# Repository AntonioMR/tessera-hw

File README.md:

<h1 align="center">Tessera Badge</h1>

<p align="center" width="100%">
  
</p>

***

<p align="center">
  
&nbsp; &nbsp; &nbsp; &nbsp;
  
</p>

***

## SPECIFICATIONS

| Parameter | Value | 
| --- | --- |
| Dimensions | 54.0 × 85.61 mm |

***

## DIRECTORY STRUCTURE

    .
    ├─ Computations       # Misc calculations
    ├─ HTML               # HTML files for generated webpage
    ├─ Images             # Pictures and renders
    │
    ├─ kibot_resources    # External resources for KiBot
    │  ├─ colors          # Color theme for KiCad
    │  ├─ fonts           # Fonts used in the project
    │  ├─ scripts         # External scripts used with KiBot
    │  └─ templates       # Templates for KiBot generated reports
    │
    ├─ kibot_yaml         # KiBot YAML config files
    ├─ KiRI               # KiRI (PCB diff viewer) files
    │
    ├─ lib                # KiCad footprint and symbol libraries
    │  ├─ lib_fp          # Footprint libraries
    │  ├─ lib_packages3d  # Component 3D models
    │  └─ lib_sym         # Symbol libraries
    │
    ├─ Logos              # Logos
    │
    ├─ Manufacturing      # Assembly and fabrication documents
    │  ├─ Assembly        # Assembly documents (BoM, pos, notes)
    │  │
    │  └─ Fabrication     # Fabrication documents (ZIP, notes)
    │     ├─ Drill Tables # CSV drill tables
    │     └─ Gerbers      # Gerbers
    │
    ├─ Report             # Reports for ERC/DRC
    ├─ Schematic          # PDF of schematic
    ├─ Templates          # Title block templates
    ├─ Testing
    │  └─ Testpoints      # Testpoints tables      
    │
    └─ Variants           # Outputs for assembly variants

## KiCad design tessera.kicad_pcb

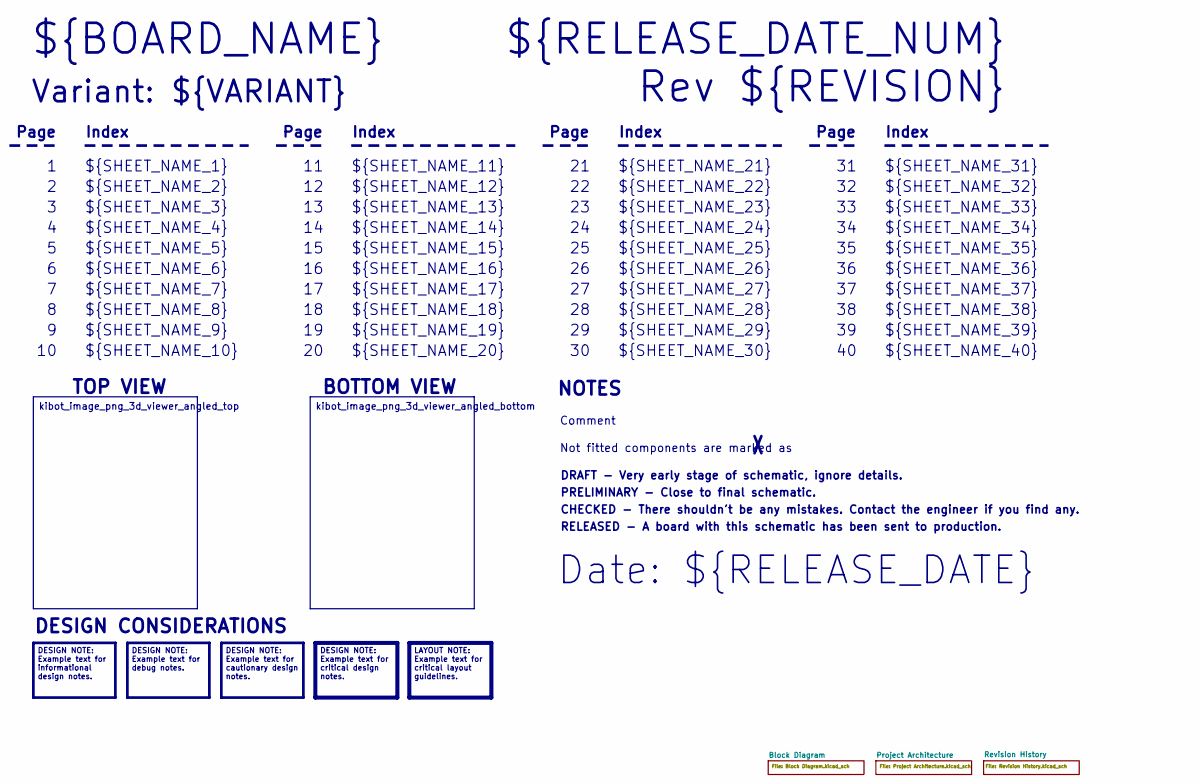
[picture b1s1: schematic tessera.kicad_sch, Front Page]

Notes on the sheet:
DESIGN NOTE: Example text for cautionary design notes.
DESIGN NOTE: Example text for debug notes.
DESIGN NOTE: Example text for critical design notes.
LAYOUT NOTE: Example text for critical layout guidelines.
kibot_image_png_3d_viewer_angled_bottom
DESIGN NOTE: Example text for informational design notes.
kibot_image_png_3d_viewer_angled_top
Variant: ${VARIANT}
RELEASED - A board with this schematic has been sent to production.
${SHEET_NAME_24}
Index
Page
PRELIMINARY - Close to final schematic.
${SHEET_NAME_22}
DRAFT - Very early stage of schematic, ignore details.
${SHEET_NAME_12}
${SHEET_NAME_8}
${SHEET_NAME_2}
${SHEET_NAME_5}
${SHEET_NAME_20}
${SHEET_NAME_23}
${RELEASE_DATE_NUM}
${SHEET_NAME_35}
Not fitted components are marked as
${SHEET_NAME_11}
${SHEET_NAME_6}
${SHEET_NAME_37}
${SHEET_NAME_26}
${SHEET_NAME_36}
Rev ${REVISION}
${SHEET_NAME_15}
CHECKED - There shouldn't be any mistakes. Contact the engineer if you find any.
BOTTOM VIEW
${SHEET_NAME_14}
${SHEET_NAME_21}
${SHEET_NAME_17}
${SHEET_NAME_18}
Date: ${RELEASE_DATE}
${SHEET_NAME_7}
${SHEET_NAME_31}

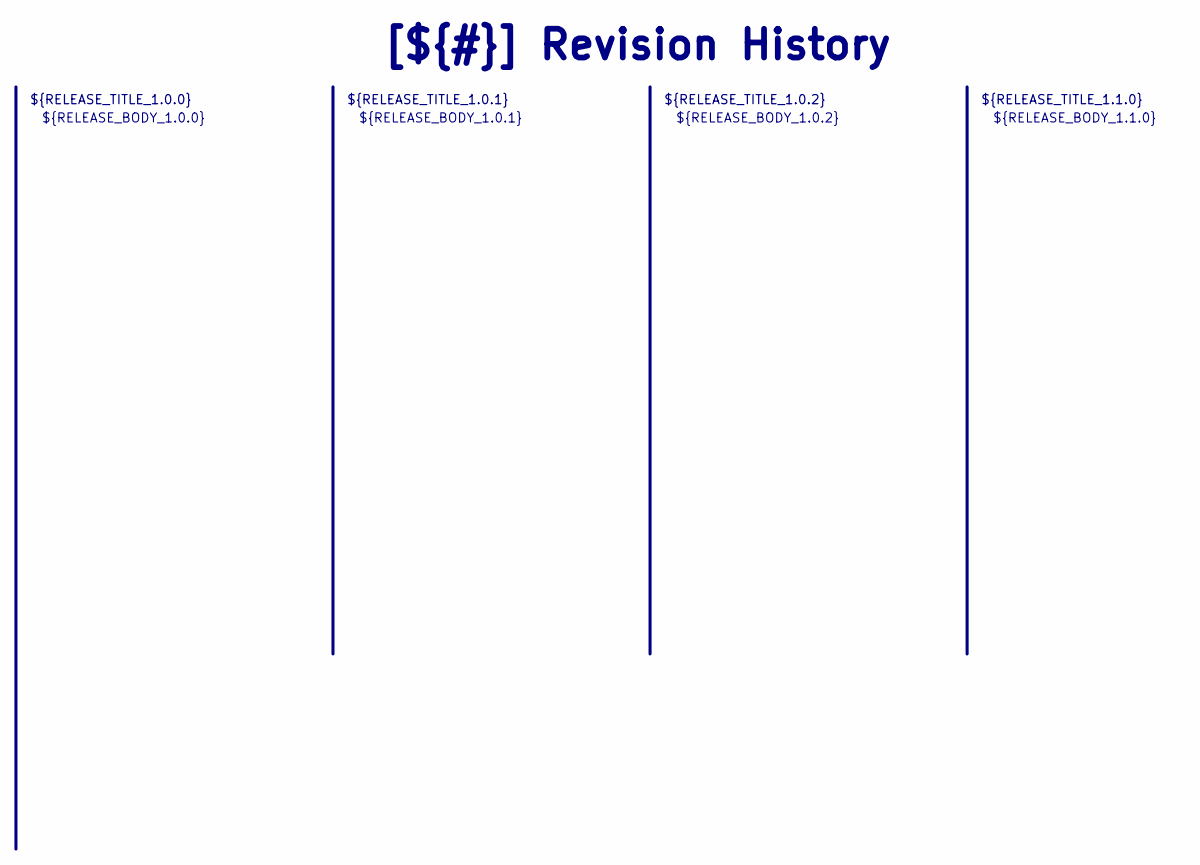
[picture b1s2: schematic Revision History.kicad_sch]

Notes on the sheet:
${RELEASE_BODY_1.1.0}
[${#}] ${TITLE}
${RELEASE_BODY_1.0.0}
${RELEASE_TITLE_1.0.2}
${RELEASE_BODY_1.0.2}
${RELEASE_BODY_1.0.1}
${RELEASE_TITLE_1.0.0}
${RELEASE_TITLE_1.0.1}
${RELEASE_TITLE_1.1.0}

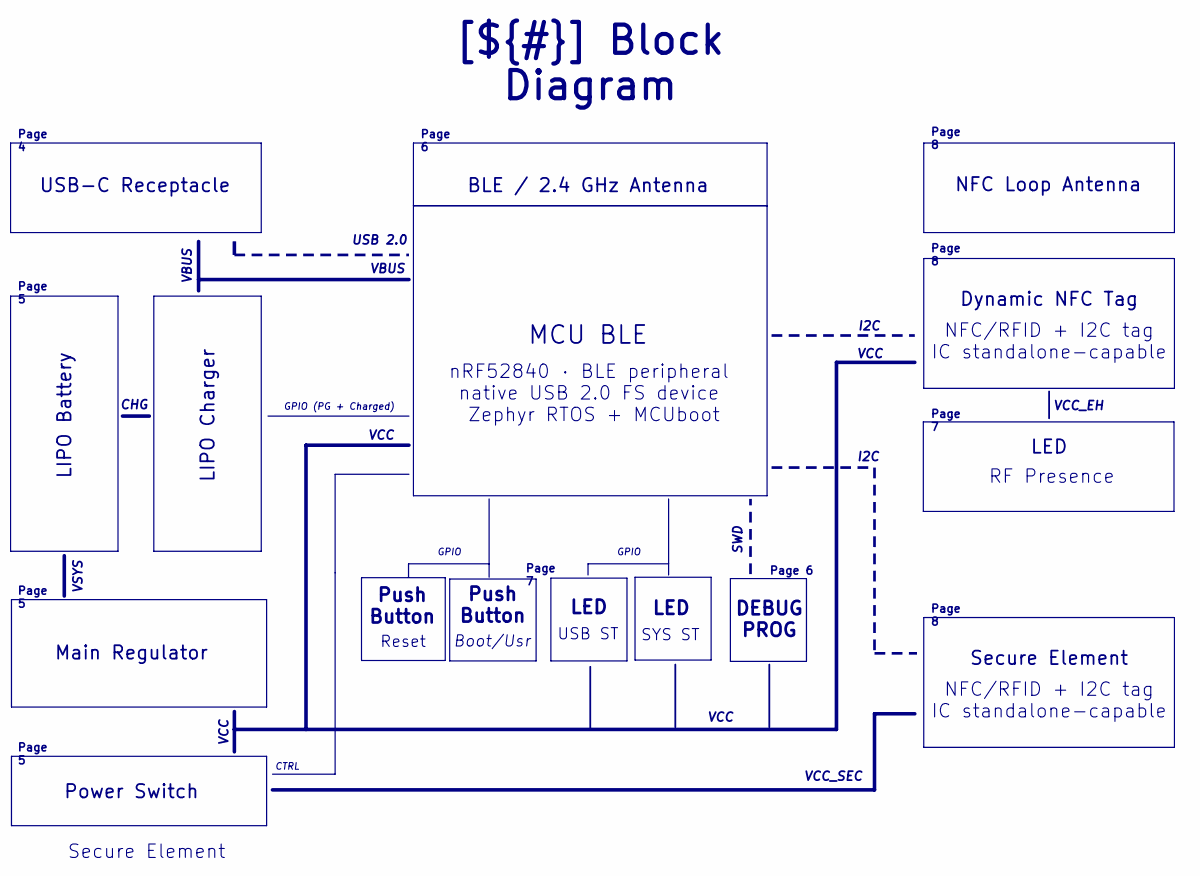
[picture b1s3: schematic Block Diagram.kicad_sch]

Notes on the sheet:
Page 5
Page 6
Page 7
[${#}] ${TITLE}
Page 4
Page 8
Reset
LED
VCC
NFC/RFID + I2C tag IC standalone-capable
USB ST
LIPO Battery
Boot/Usr
I2C
VCC_EH
Dynamic NFC Tag
VBUS
VSYS
CTRL
Secure Element
SYS ST
MCU BLE
BLE / 2.4 GHz Antenna
USB-C Receptacle
Main Regulator
GPIO
GPIO (PG + Charged)
VCC_SEC
Push Button
SWD
LIPO Charger
CHG
NFC Loop Antenna
Secure Element
USB 2.0
nRF52840 · BLE peripheral native USB 2.0 FS device Zephyr RTOS + MCUboot
RF Presence
DEBUG PROG
Power Switch

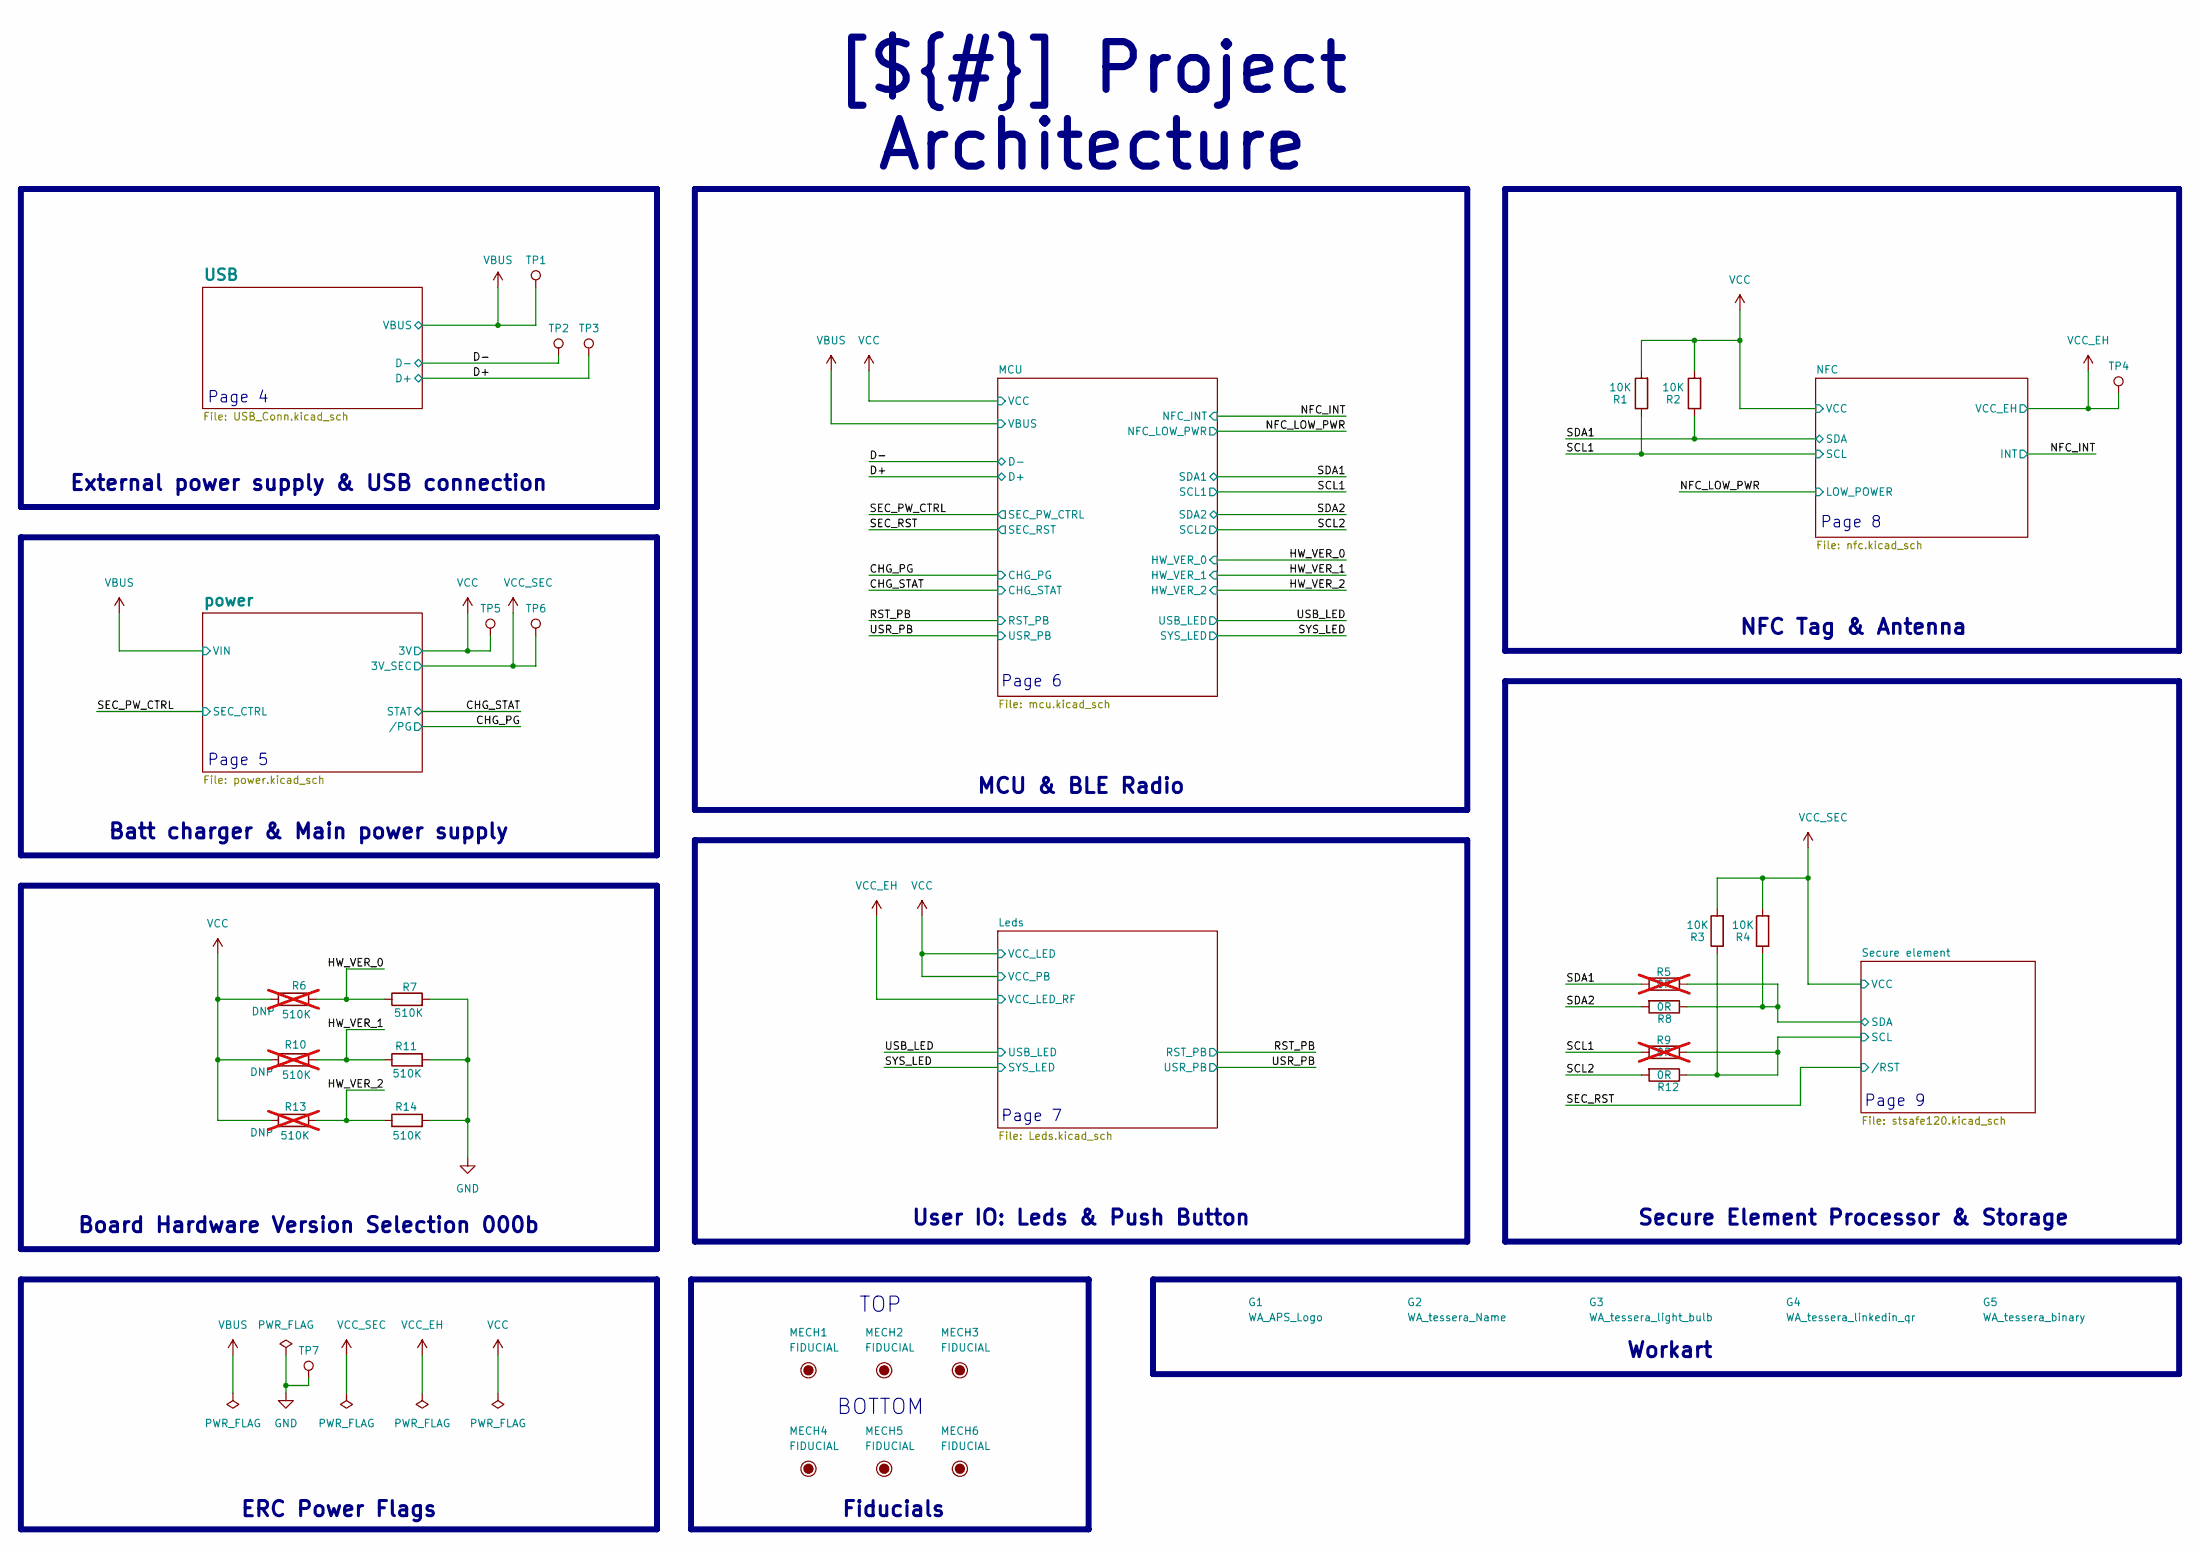
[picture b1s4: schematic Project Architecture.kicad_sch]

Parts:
G1: WA_APS_Logo; logo_aps_4_5
G2: WA_tessera_Name; Name
G3: WA_tessera_light_bulb; light_bulb_8_7_12
G4: WA_tessera_linkedin_qr; linkedin_qr_with_linkedin_logo_inv
G5: WA_tessera_binary; bin_logo
MECH1, MECH2, MECH3, MECH4, MECH5, MECH6: FIDUCIAL; Fiducial_1mm_Mask2mm; Part Number FIDUCIAL_D1_0mm_Mask_2_0mm
R1, R2, R3, R4: 10 kOhms; R_0402_1005Metric; Tolerance ±1%; Part Number R0402_10K_0.063W_±1%
R5, R9: 0R ±5% 1/16W; R_0402_1005Metric; Part Number R0402_0R_0.1W_±5%; not fitted
R6, R10, R13: 510 kOhms; R_0402_1005Metric; Tolerance ±1%; Part Number R0402_510K_0.063W_±1%; not fitted
R7, R11, R14: 510 kOhms; R_0402_1005Metric; Tolerance ±1%; Part Number R0402_510K_0.063W_±1%
R8, R12: 0R ±5% 1/16W; R_0402_1005Metric; Part Number R0402_0R_0.1W_±5%
TP1, TP2, TP3, TP4, TP5, TP6, TP7: TP; TestPoint_Pad_D1.0mm; Part Number TP_SMD_D1_0mm

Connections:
/Project Architecture/D+: TP3.1; also elsewhere on the board
/Project Architecture/D-: TP2.1; also elsewhere on the board
/Project Architecture/HW_VER_0: R6.2, R7.1; also elsewhere on the board
/Project Architecture/HW_VER_1: R10.2, R11.1; also elsewhere on the board
/Project Architecture/HW_VER_2: R13.2, R14.1; also elsewhere on the board
/Project Architecture/SCL1: R1.1, R9.1; also elsewhere on the board
/Project Architecture/SCL2: R12.2; also elsewhere on the board
/Project Architecture/SDA1: R2.1, R5.1; also elsewhere on the board
/Project Architecture/SDA2: R8.2; also elsewhere on the board
/Project Architecture/Secure element/SCL: R3.1, R9.2, R12.1; also elsewhere on the board
/Project Architecture/Secure element/SDA: R4.1, R5.2, R8.1; also elsewhere on the board
GND: R7.2, R11.2, R14.2, TP7.1; also elsewhere on the board
VBUS: TP1.1; also elsewhere on the board
VCC: R1.2, R2.2, R6.1, R10.1, R13.1, TP5.1; also elsewhere on the board
VCC_EH: TP4.1; also elsewhere on the board
VCC_SEC: R3.2, R4.2, TP6.1; also elsewhere on the board

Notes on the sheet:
Board Hardware Version Selection 000b
NFC Tag & Antenna
MCU & BLE Radio
User IO: Leds & Push Button
BOTTOM
TOP
Batt charger & Main power supply
Secure Element Processor & Storage
ERC Power Flags
External power supply & USB connection
Fiducials
Workart
[${#}] ${TITLE}
Page 9
Page 7
Page 6
Page 5
Page 8
Page 4

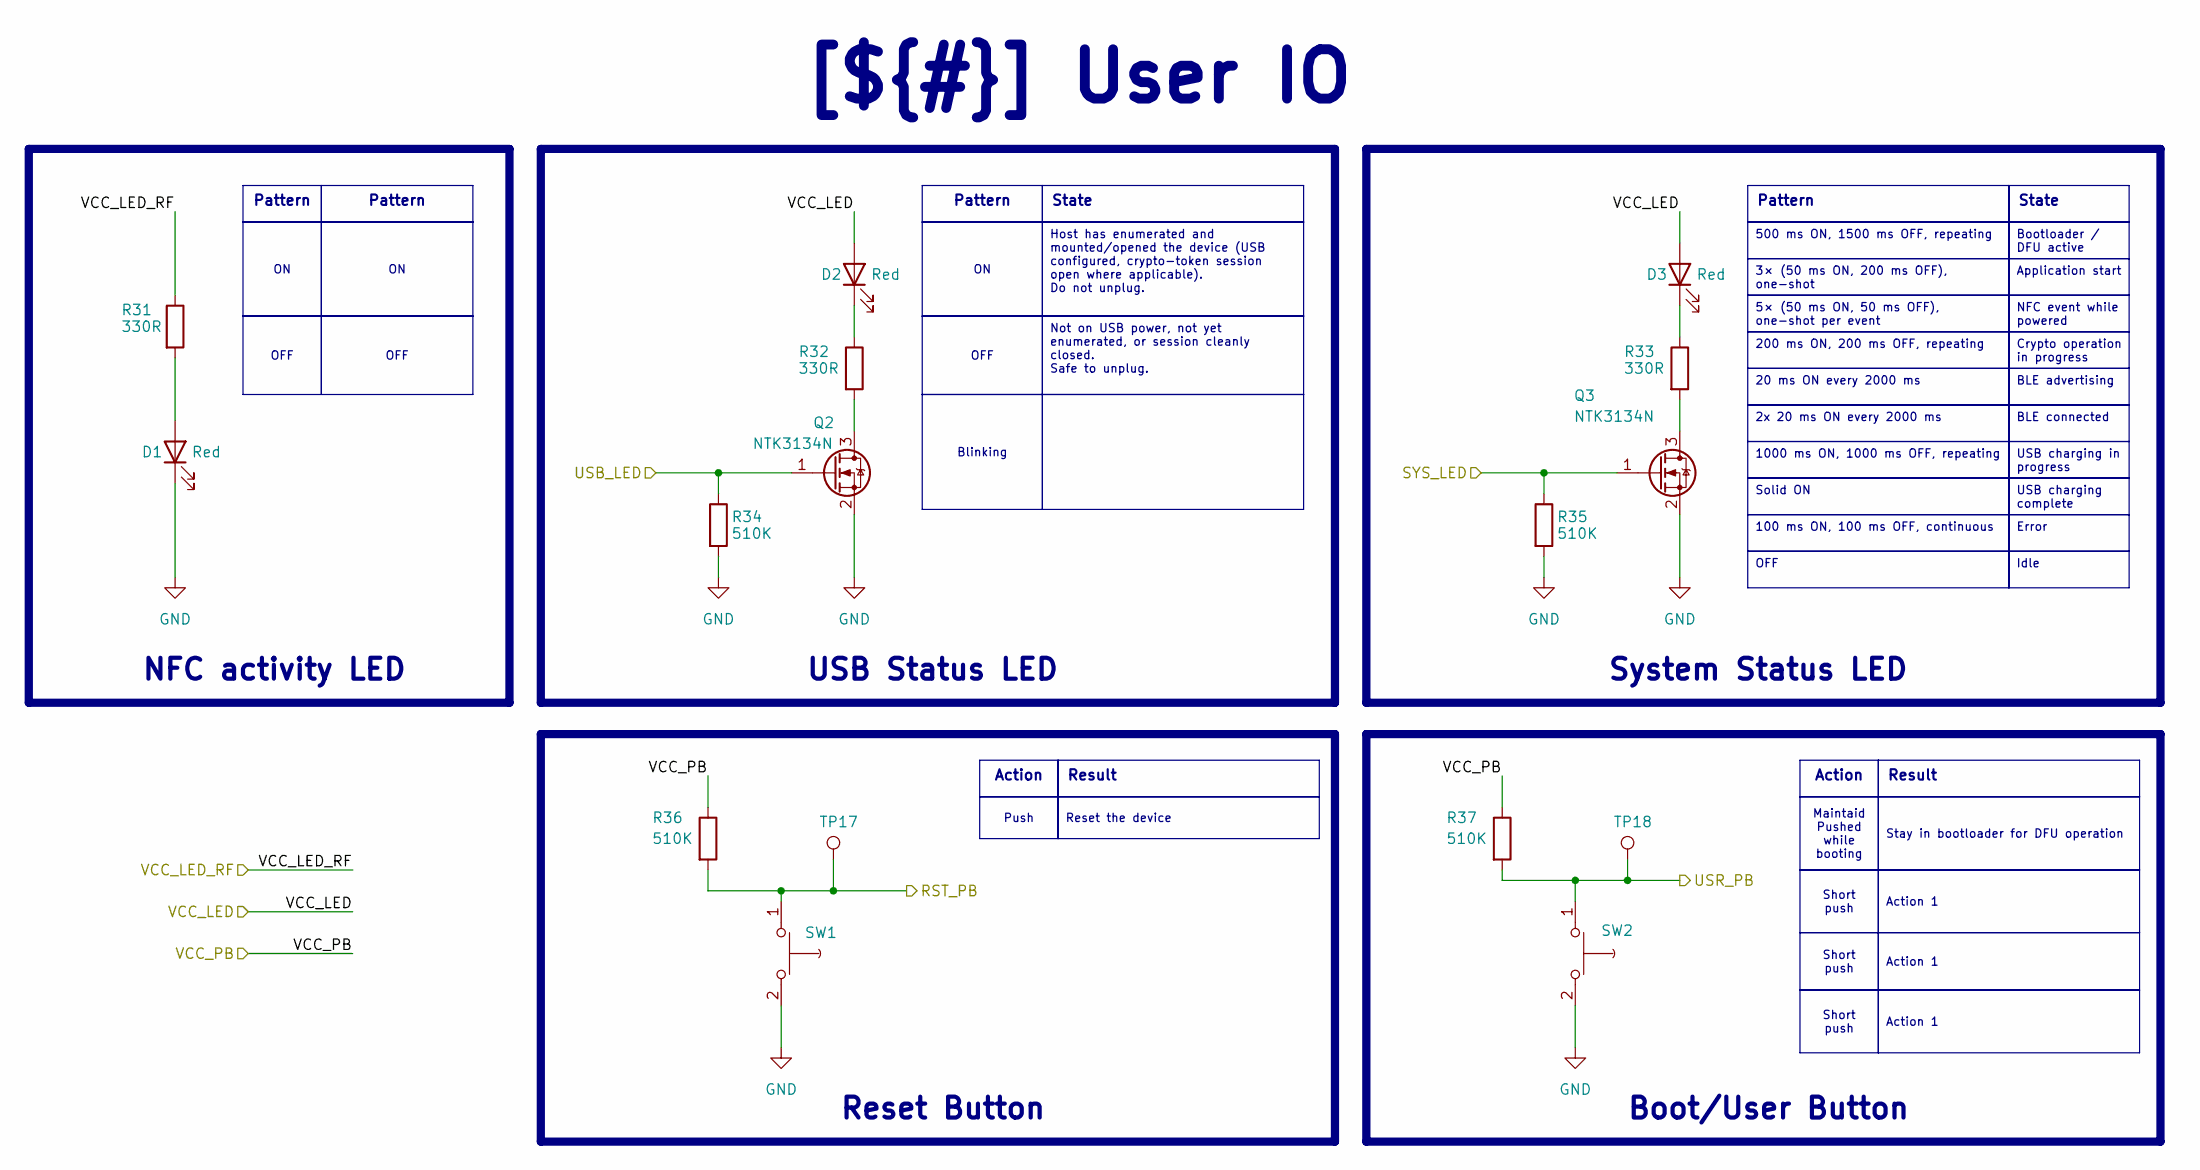
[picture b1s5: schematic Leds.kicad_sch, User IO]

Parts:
D1, D2, D3: APHHS1005SURCK; LED_0402_1005Metric; Part Number APHHS1005SURCK
Q2, Q3: NTK3134N; SOT-723; Part Number NTK3134N
R31, R32, R33: 330R ±1% 1/10W; R_0603_1608Metric; Tolerance ±1%; Part Number R0603_330R_0.1W_±1%
R34, R35, R36, R37: 510 kOhms; R_0402_1005Metric; Tolerance ±1%; Part Number R0402_510K_0.063W_±1%
SW1, SW2: EVQP7A01P; Panasonic_switch_EVQP7K_EVQP7A; Part Number EVQP7A01P
TP17, TP18: TP; TestPoint_Pad_D1.0mm; Part Number TP_SMD_D1_0mm

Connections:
/Project Architecture/RST_PB: R36.2, SW1.1, TP17.1; also elsewhere on the board
/Project Architecture/SYS_LED: Q3.1 (G), R35.1; also elsewhere on the board
/Project Architecture/USB_LED: Q2.1 (G), R34.1; also elsewhere on the board
/Project Architecture/USR_PB: R37.2, SW2.1, TP18.1; also elsewhere on the board
GND: D1.1 (K), Q2.2 (S), Q3.2 (S), R34.2, R35.2, SW1.2, SW2.2; also elsewhere on the board
unnamed: D1.2 (A), R31.2
unnamed: D2.1 (K), R32.1
unnamed: D3.1 (K), R33.1
unnamed: Q2.3 (D), R32.2
unnamed: Q3.3 (D), R33.2
VCC: D2.2 (A), D3.2 (A), R36.1, R37.1; also elsewhere on the board
VCC_EH: R31.1; also elsewhere on the board

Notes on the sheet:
State
OFF
USB charging in progress
Application start
Error
3× (50 ms ON, 200 ms OFF), one-shot
Bootloader / DFU active
Result
Action 1
Short push
Blinking
Solid ON
BLE advertising
Pattern
100 ms ON, 100 ms OFF, continuous
Reset the device
NFC activity LED
USB Status LED
Idle
Action
20 ms ON every 2000 ms
[${#}] ${TITLE}
Boot/User Button
Not on USB power, not yet enumerated, or session cleanly closed. Safe to unplug.
Crypto operation in progress
Host has enumerated and mounted/opened the device (USB configured, crypto-token session open where applicable). Do not unplug.
System Status LED
Maintaid Pushed while booting
Push
Reset Button
2x 20 ms ON every 2000 ms
1000 ms ON, 1000 ms OFF, repeating
USB charging complete
NFC event while powered
BLE connected
500 ms ON, 1500 ms OFF, repeating
Stay in bootloader for DFU operation
200 ms ON, 200 ms OFF, repeating
5× (50 ms ON, 50 ms OFF), one-shot per event

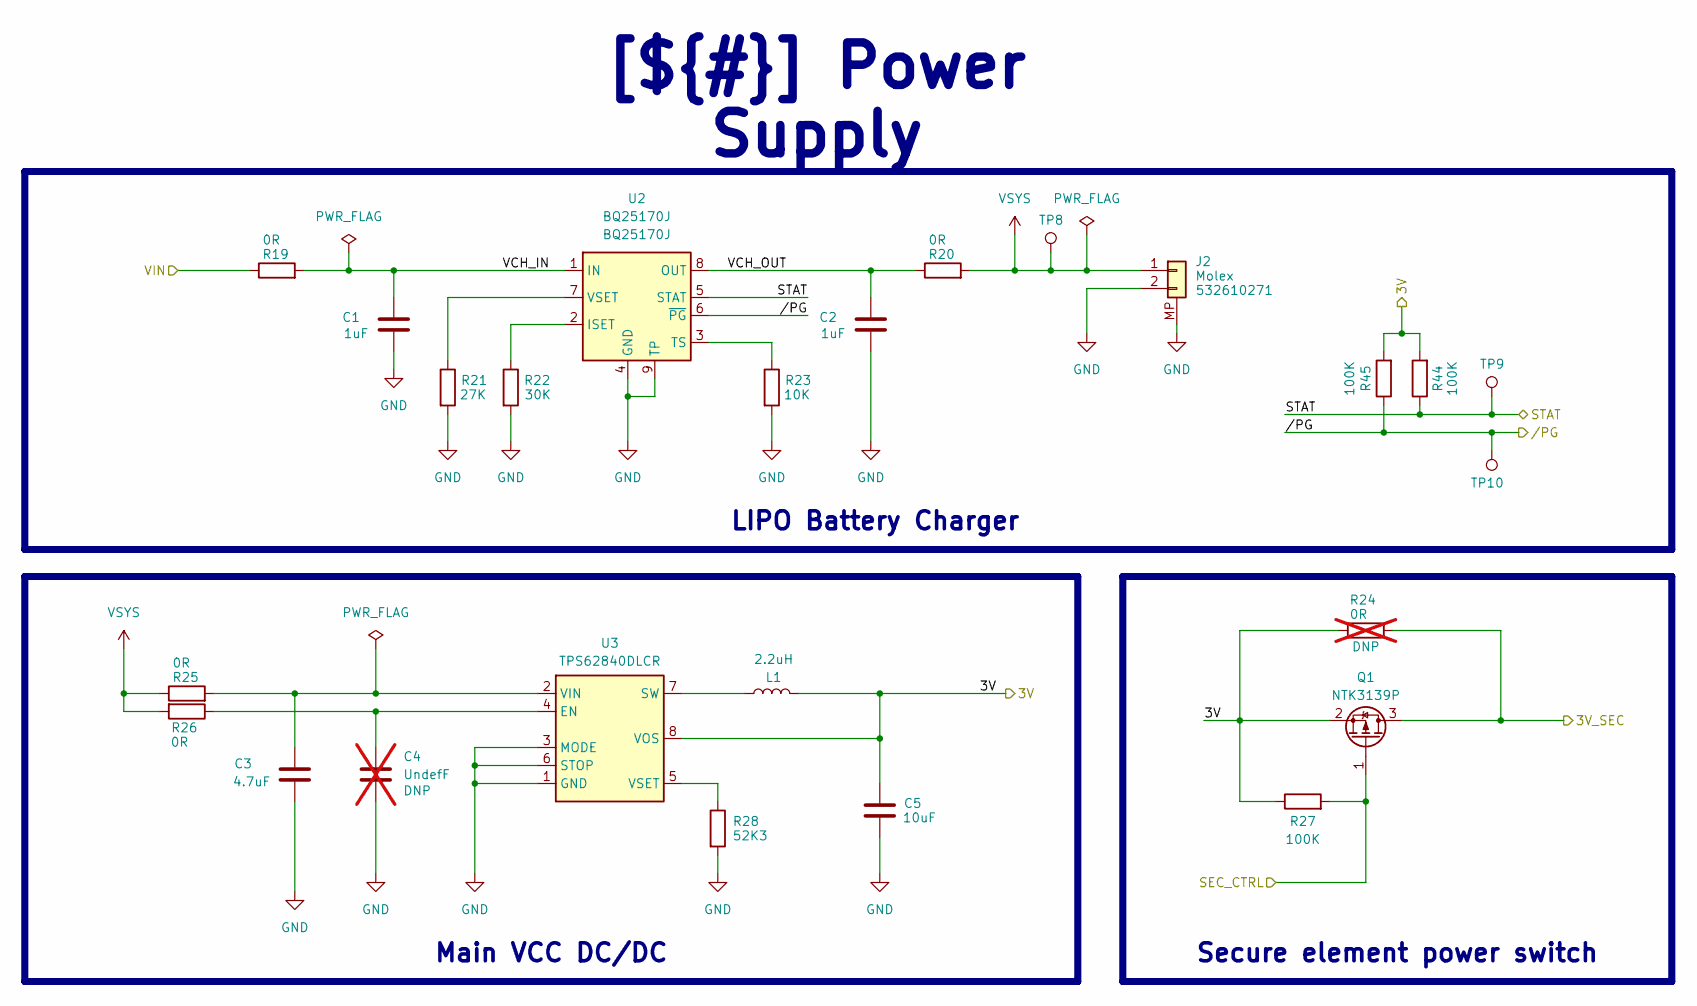
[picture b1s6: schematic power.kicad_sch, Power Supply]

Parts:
C1, C2: 1uF 6.3V (X5R); C_0402_1005Metric; Tolerance ±10%; Voltage 6.3V; Part Number C0402_1uF_6.3V_±10%_X5R
C3: 4.7uF 6.3V (X7R); C_0805_2012Metric; Tolerance ±10%; Voltage 6.3V; Part Number C0805_4.7uF_6.3V_±10%_X7R
C4: UndefF; C_0402_1005Metric; Part Number C0402_Undef; not fitted
C5: 10uF 10V (X7R); C_0805_2012Metric; Tolerance ±10%; Voltage 10V; Part Number C0805_10uF_10V_±10%_X7R
J2: 532610271; Molex_PicoBlade_53261-0271_1x02-1MP_P1.25mm_Horizontal; Voltage 125V; Part Number Molex_PicoBlade_532610271
L1: 2.2uH; L_0806_2016Metric; Tolerance ±20%; Part Number L0806_2.2uH_1.8A_±20%_116mOhm
Q1: NTK3139P; SOT-723; Part Number NTK3139P
R19, R20, R25, R26: 0R ±5% 1/16W; R_0402_1005Metric; Part Number R0402_0R_0.1W_±5%
R21: 27 kOhms; R_0402_1005Metric; Tolerance ±1%; Part Number R0402_27K_0.063W_±1%
R22: 30 kOhms; R_0402_1005Metric; Tolerance ±1%; Part Number R0402_30K_0.063W_±1%
R23: 10 kOhms; R_0402_1005Metric; Tolerance ±1%; Part Number R0402_10K_0.063W_±1%
R24: 0R ±5% 1/16W; R_0402_1005Metric; Part Number R0402_0R_0.1W_±5%; not fitted
R27, R44, R45: 100 kOhms; R_0402_1005Metric; Tolerance ±1%; Part Number R0402_100K_0.063W_±1%
R28: 52.3 kOhms; R_0402_1005Metric; Tolerance ±1%; Part Number R0402_52K3_0.063W_±1%
TP8, TP9, TP10: TP; TestPoint_Pad_D1.0mm; Part Number TP_SMD_D1_0mm
U2: BQ25170J; WSON-8-1EP_2x2mm_P0.5mm_EP0.9x1.6mm; Part Number BQ25170J
U3: TPS62840DLCR; Texas_VSON-HR-8_1.5x2mm_P0.5mm; Part Number TPS62840DLCR

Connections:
/Project Architecture/CHG_PG: R45.1, TP10.1, U2.6 (~PG); also elsewhere on the board
/Project Architecture/CHG_STAT: R44.1, TP9.1, U2.5 (STAT); also elsewhere on the board
/Project Architecture/SEC_PW_CTRL: Q1.1 (G), R27.2; also elsewhere on the board
/Project Architecture/power/VCH_IN: C1.1, R19.2, U2.1 (IN)
/Project Architecture/power/VCH_OUT: C2.1, R20.1, U2.8 (OUT)
GND: C1.2, C2.2, C3.2, C4.2, C5.2, J2.2, J2.MP, R21.2, R22.2, R23.2, R28.2, U2.4 (GND), U2.9 (TP), U3.1 (GND), U3.3 (MODE), U3.6 (STOP); also elsewhere on the board
unnamed: R22.1, U2.2 (ISET)
unnamed: R23.1, U2.3 (TS)
unnamed: R21.1, U2.7 (VSET)
unnamed: C4.1, R26.1, U3.4 (EN)
unnamed: L1.1, U3.7 (SW)
unnamed: C3.1, R25.2, U3.2 (VIN)
unnamed: R28.1, U3.5 (VSET)
VBUS: R19.1; also elsewhere on the board
VCC: C5.1, L1.2, Q1.2 (S), R24.1, R27.1, R44.2, R45.2, U3.8 (VOS); also elsewhere on the board
VCC_SEC: Q1.3 (D), R24.2; also elsewhere on the board
VSYS: J2.1, R20.2, R25.1, R26.2, TP8.1

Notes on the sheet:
LIPO Battery Charger
Secure element power switch
Main VCC DC/DC
[${#}] ${TITLE}

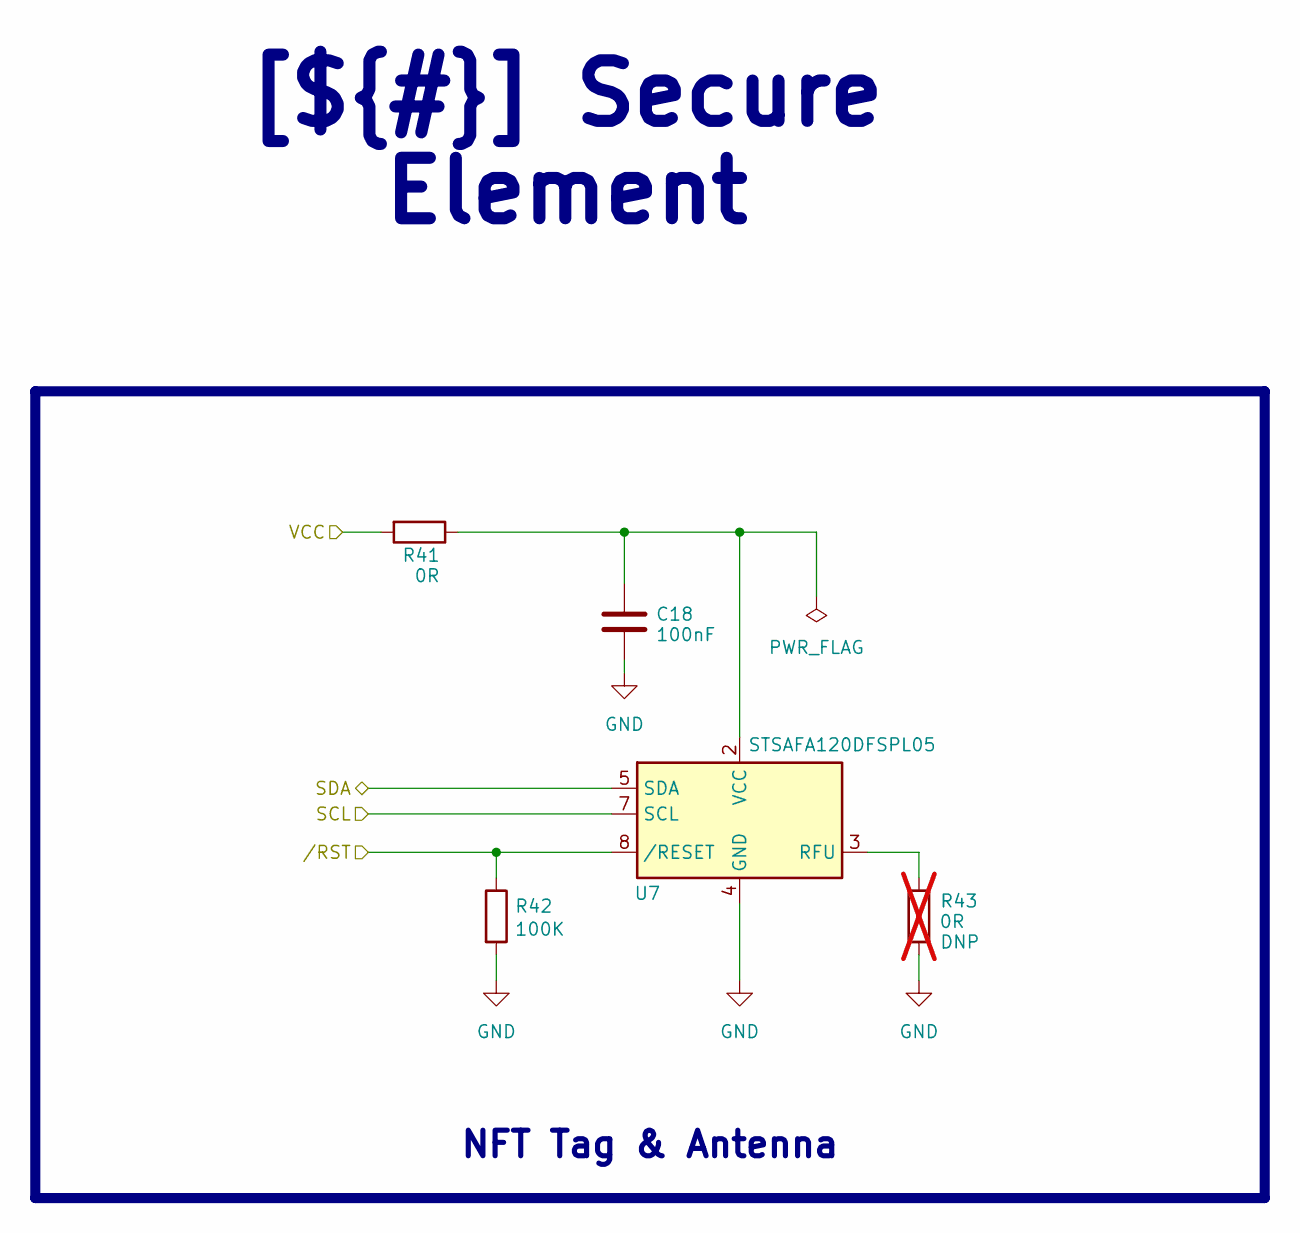
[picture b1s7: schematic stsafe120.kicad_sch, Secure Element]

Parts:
C18: 100nF 16V (X7R); C_0402_1005Metric; Tolerance ±10%; Voltage 16V; Part Number C0402_100nF_16V_±10%_X7R
R41: 0R ±5% 1/16W; R_0402_1005Metric; Part Number R0402_0R_0.1W_±5%
R42: 100 kOhms; R_0402_1005Metric; Tolerance ±1%; Part Number R0402_100K_0.063W_±1%
R43: 0R ±5% 1/16W; R_0402_1005Metric; Part Number R0402_0R_0.1W_±5%; not fitted
U7: STSAFA120DFSPL05; ST_UFDFPN-8-1EP_2x3mm_P0.5mm_EP1.4x2.55mm; Voltage 2.7-5.5 V; Part Number STSAFA120DFSPL05

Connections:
/Project Architecture/SEC_RST: R42.1, U7.8 (/RESET); also elsewhere on the board
/Project Architecture/Secure element/SCL: U7.7 (SCL); also elsewhere on the board
/Project Architecture/Secure element/SDA: U7.5 (SDA); also elsewhere on the board
GND: C18.2, R42.2, R43.2, U7.4 (GND), U7.9 (EP); also elsewhere on the board
unnamed: R43.1, U7.3 (RFU)
unnamed: C18.1, R41.1, U7.2 (VCC)
VCC_SEC: R41.2; also elsewhere on the board

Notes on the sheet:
[${#}] ${TITLE}
NFT Tag & Antenna

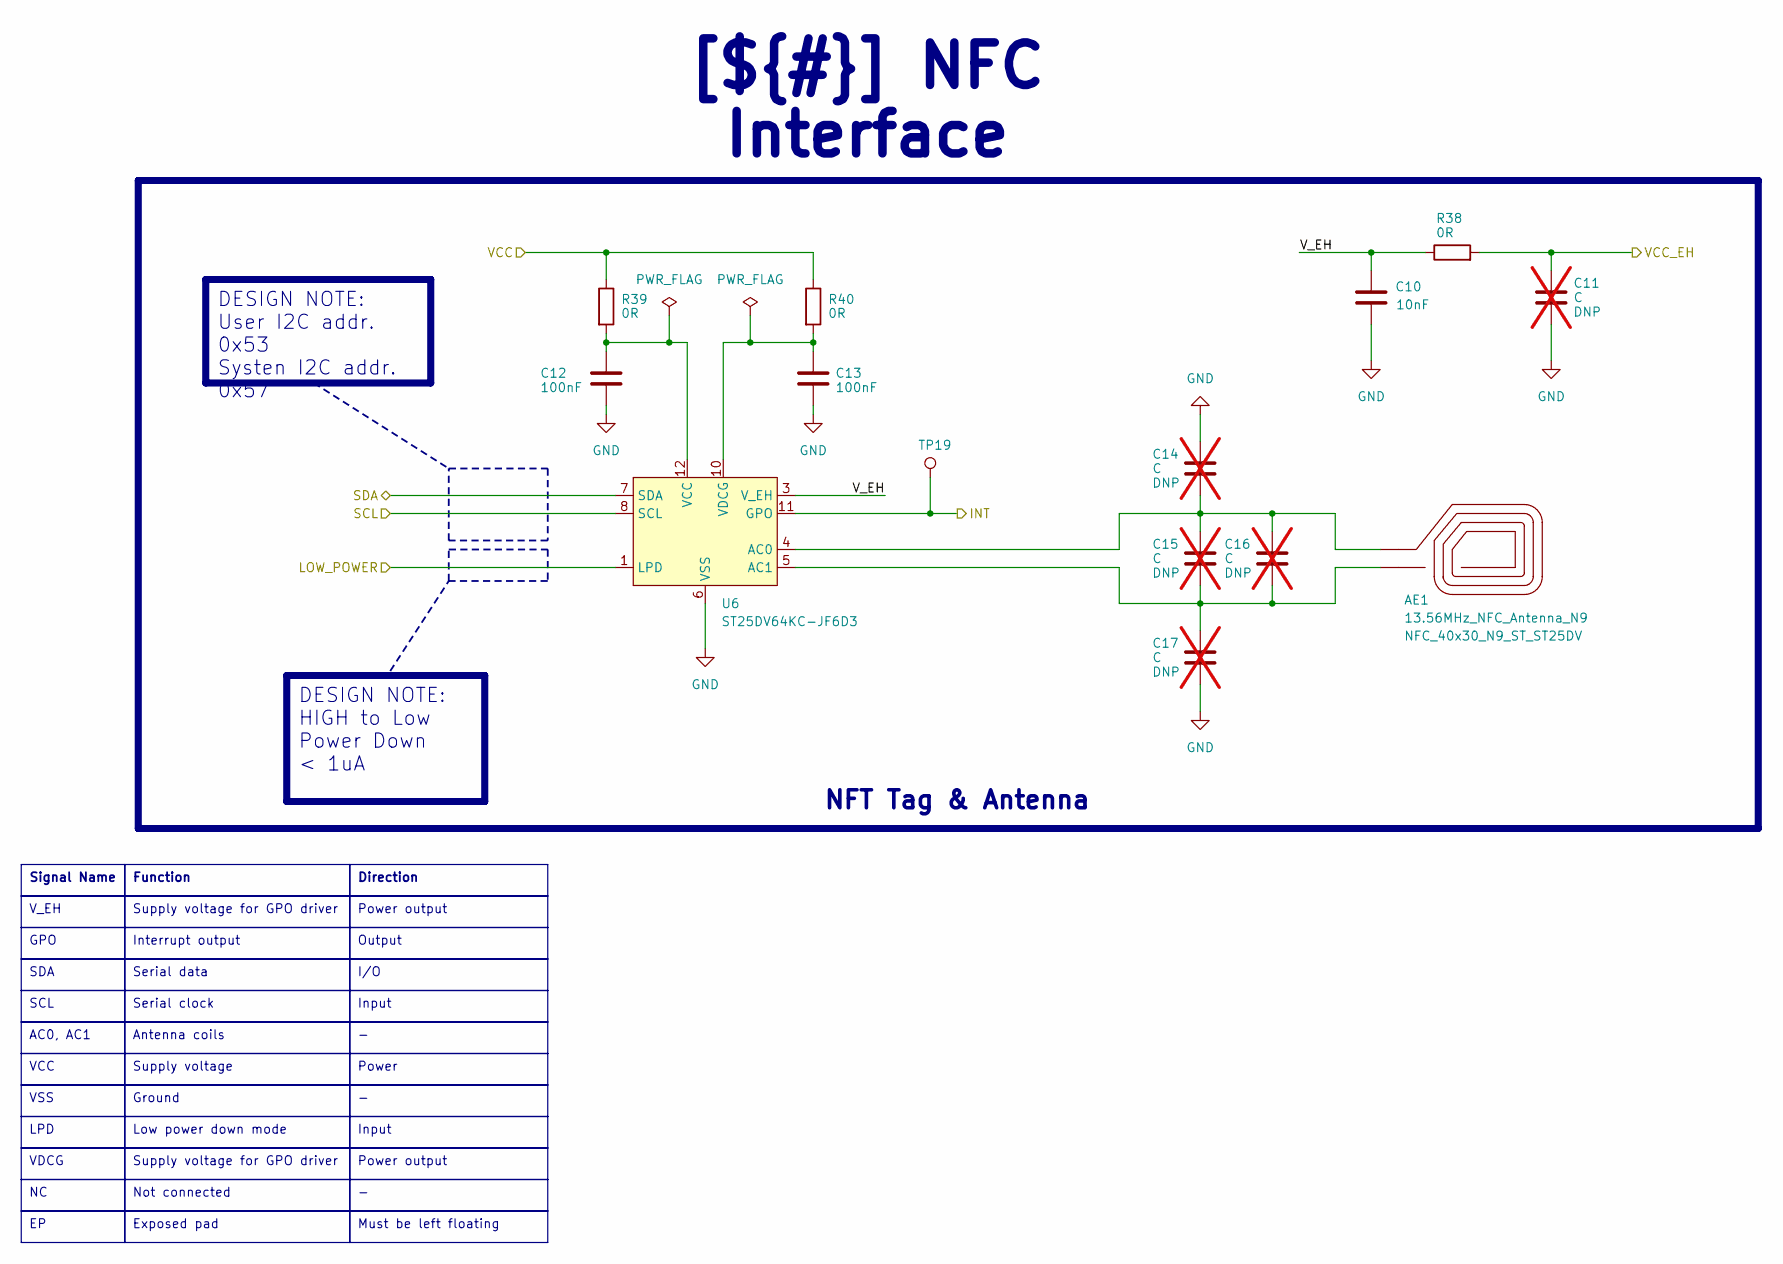
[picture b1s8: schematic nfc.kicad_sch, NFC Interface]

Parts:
AE1: 13.56MHz_NFC_Antenna_N9; NFC_40x30_N9_ST_ST25DV; Part Number NFC_40x30_N9_ST_ST25DV
C10: 10nF 16V (X7R); C_0402_1005Metric; Tolerance ±10%; Voltage 16V; Part Number C0402_10nF_16V_±10%_X7R
C11, C14, C15, C16, C17: UndefF; C_0402_1005Metric; Part Number C0402_Undef; not fitted
C12, C13: 100nF 16V (X7R); C_0402_1005Metric; Tolerance ±10%; Voltage 16V; Part Number C0402_100nF_16V_±10%_X7R
R38, R39, R40: 0R ±5% 1/16W; R_0402_1005Metric; Part Number R0402_0R_0.1W_±5%
TP19: TP; TestPoint_Pad_D1.0mm; Part Number TP_SMD_D1_0mm
U6: ST25DV64KC-JF6D3; ST_UFDFPN-12-1EP_3x3mm_P0.5mm_EP1.4x2.55mm; Voltage 1.8-5.5 V; Part Number ST25DV64KC-JF6D3

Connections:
/Project Architecture/NFC/V_EH: C10.1, R38.1, U6.3 (V_EH)
/Project Architecture/NFC_INT: TP19.1, U6.11 (GPO); also elsewhere on the board
/Project Architecture/NFC_LOW_PWR: U6.1 (LPD); also elsewhere on the board
/Project Architecture/SCL1: U6.8 (SCL); also elsewhere on the board
/Project Architecture/SDA1: U6.7 (SDA); also elsewhere on the board
GND: C10.2, C11.2, C12.2, C13.2, C14.1, C17.2, U6.6 (VSS); also elsewhere on the board
unnamed: AE1.2 (INNER), C15.2, C16.2, C17.1, U6.5 (AC1)
unnamed: AE1.1 (OUTER), C14.2, C15.1, C16.1, U6.4 (AC0)
unnamed: C12.1, R39.2, U6.12 (VCC)
unnamed: C13.1, R40.2, U6.10 (VDCG)
VCC: R39.1, R40.1; also elsewhere on the board
VCC_EH: C11.1, R38.2; also elsewhere on the board

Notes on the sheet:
GPO
Input
Exposed pad
Power output
VDCG
LPD
DESIGN NOTE: User I2C addr. 0x53 Systen I2C addr. 0x57
Serial clock
V_EH
VCC
Interrupt output
Ground
Supply voltage for GPO driver
VSS
Signal Name
Function
Supply voltage
I/O
Output
Not connected
Serial data
SCL
DESIGN NOTE: HIGH to Low Power Down < 1uA
Power
SDA
AC0, AC1
[${#}] ${TITLE}
Low power down mode
NFT Tag & Antenna
Must be left floating
Antenna coils
Direction

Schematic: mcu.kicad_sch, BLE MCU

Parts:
C6, C8: 10uF 10V (X7R); C_0805_2012Metric; Tolerance ±10%; Voltage 10V; Part Number C0805_10uF_10V_±10%_X7R
C7, C9: 100nF 16V (X7R); C_0402_1005Metric; Tolerance ±10%; Voltage 16V; Part Number C0402_100nF_16V_±10%_X7R
J3: PinHeader_2x05; PinHeader_2x05_P1.27mm_Vertical_SMD_TRH; Voltage 200VAC; Part Number PinHeader_2x05_P1.27mm_Vertical_SMD; not fitted
R29, R30: 0R ±5% 1/16W; R_0402_1005Metric; Part Number R0402_0R_0.1W_±5%
TP11, TP12, TP13, TP14, TP15, TP16: TP; TestPoint_Pad_D1.0mm; Part Number TP_SMD_D1_0mm
U4: ISP1807-LR-RS; ISP1807-LR; Voltage 1.7-5.5 V; Part Number ISP1807-LR
U5: D3V3XA4B10LP; Diodes_UDFN-10_1.0x2.5mm_P0.5mm; Part Number D3V3XA4B10LP

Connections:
/Project Architecture/CHG_PG: U4.29 (P0_13); also elsewhere on the board
/Project Architecture/CHG_STAT: U4.35 (P0_04_AIN2); also elsewhere on the board
/Project Architecture/D+: U4.8 (D+); also elsewhere on the board
/Project Architecture/D-: U4.10 (D-); also elsewhere on the board
/Project Architecture/HW_VER_0: U4.46 (P0_29_AIN5); also elsewhere on the board
/Project Architecture/HW_VER_1: U4.48 (P0_28_AIN4); also elsewhere on the board
/Project Architecture/HW_VER_2: U4.44 (P0_30_AIN6); also elsewhere on the board
/Project Architecture/MCU/SWDCLK: J3.4, TP14.1, U4.30 (SWDCLK), U5.4, U5.7
/Project Architecture/MCU/SWDIO: J3.2, TP16.1, U4.28 (SWDIO), U5.5, U5.6
/Project Architecture/MCU/SWDO: J3.6, TP15.1, U4.57 (P1_00_TRACEDATA0), U5.2, U5.9
/Project Architecture/MCU/UART_RX: J3.8, U4.15 (P0_20)
/Project Architecture/MCU/UART_TX: J3.7, U4.17 (P0_22)
/Project Architecture/NFC_INT: U4.42 (P0_31_AIN7); also elsewhere on the board
/Project Architecture/NFC_LOW_PWR: U4.37 (P0_15); also elsewhere on the board
/Project Architecture/RST_PB: J3.10, TP13.1, U4.13 (P0_18_RESET), U5.1, U5.10; also elsewhere on the board
/Project Architecture/SCL1: U4.34 (P0_06); also elsewhere on the board
/Project Architecture/SCL2: U4.36 (P0_05_AIN3); also elsewhere on the board
/Project Architecture/SDA1: U4.38 (P0_03_AIN1); also elsewhere on the board
/Project Architecture/SDA2: U4.40 (P0_02_AIN0); also elsewhere on the board
/Project Architecture/SEC_PW_CTRL: U4.27 (P0_17); also elsewhere on the board
/Project Architecture/SEC_RST: U4.32 (P0_08); also elsewhere on the board
/Project Architecture/SYS_LED: U4.47 (P0_23); also elsewhere on the board
/Project Architecture/USB_LED: U4.45 (P0_19); also elsewhere on the board
/Project Architecture/USR_PB: U4.41 (P0_25); also elsewhere on the board
GND: C6.2, C7.2, C8.2, C9.2, J3.3, J3.5, J3.9, U4.1 (VSS), U4.7 (VSS), U4.14 (VSS), U4.16 (VSS), U4.18 (VSS), U4.21 (VSS), U4.23 (VSS), U4.24 (VSS), U4.25 (VSS), U4.31 (VSS), U5.3 (VSS), U5.8 (VSS); also elsewhere on the board
unnamed: U4.20 (OUT_ANT), U4.22 (OUT_MOD)
VBUS: R30.1; also elsewhere on the board
VBUS_nRF: C8.1, C9.1, R30.2, TP12.1, U4.12 (VBUS)
VCC: R29.1; also elsewhere on the board
VCC_nRF: C6.1, C7.1, J3.1, R29.2, TP11.1, U4.26 (VCC_NRF)

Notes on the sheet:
Debug & Program interface
DESIGN NOTE:
MCU Power supply
Main MCU
LAYOUT NOTE: prioritise the use of the package's external pins
[${#}] ${TITLE}
